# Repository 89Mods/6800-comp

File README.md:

# 6800-comp

Computer with a 6800 (or 6809) CPU. See [here](https://tholin.dev/6800/) for more information.

`Emu` contains an emulation of the computer (6800 mode only) written in C++.

`Hardware` contains the KiCad projects for all the boards.

`Kernal` contains the kernal sources that go on the EPROM.

`Software` contains all kinds of software I’ve written for this computer.

The [ASL Assembler](https://github.com/Macroassembler-AS/asl-releases) is required to build all code in this project.

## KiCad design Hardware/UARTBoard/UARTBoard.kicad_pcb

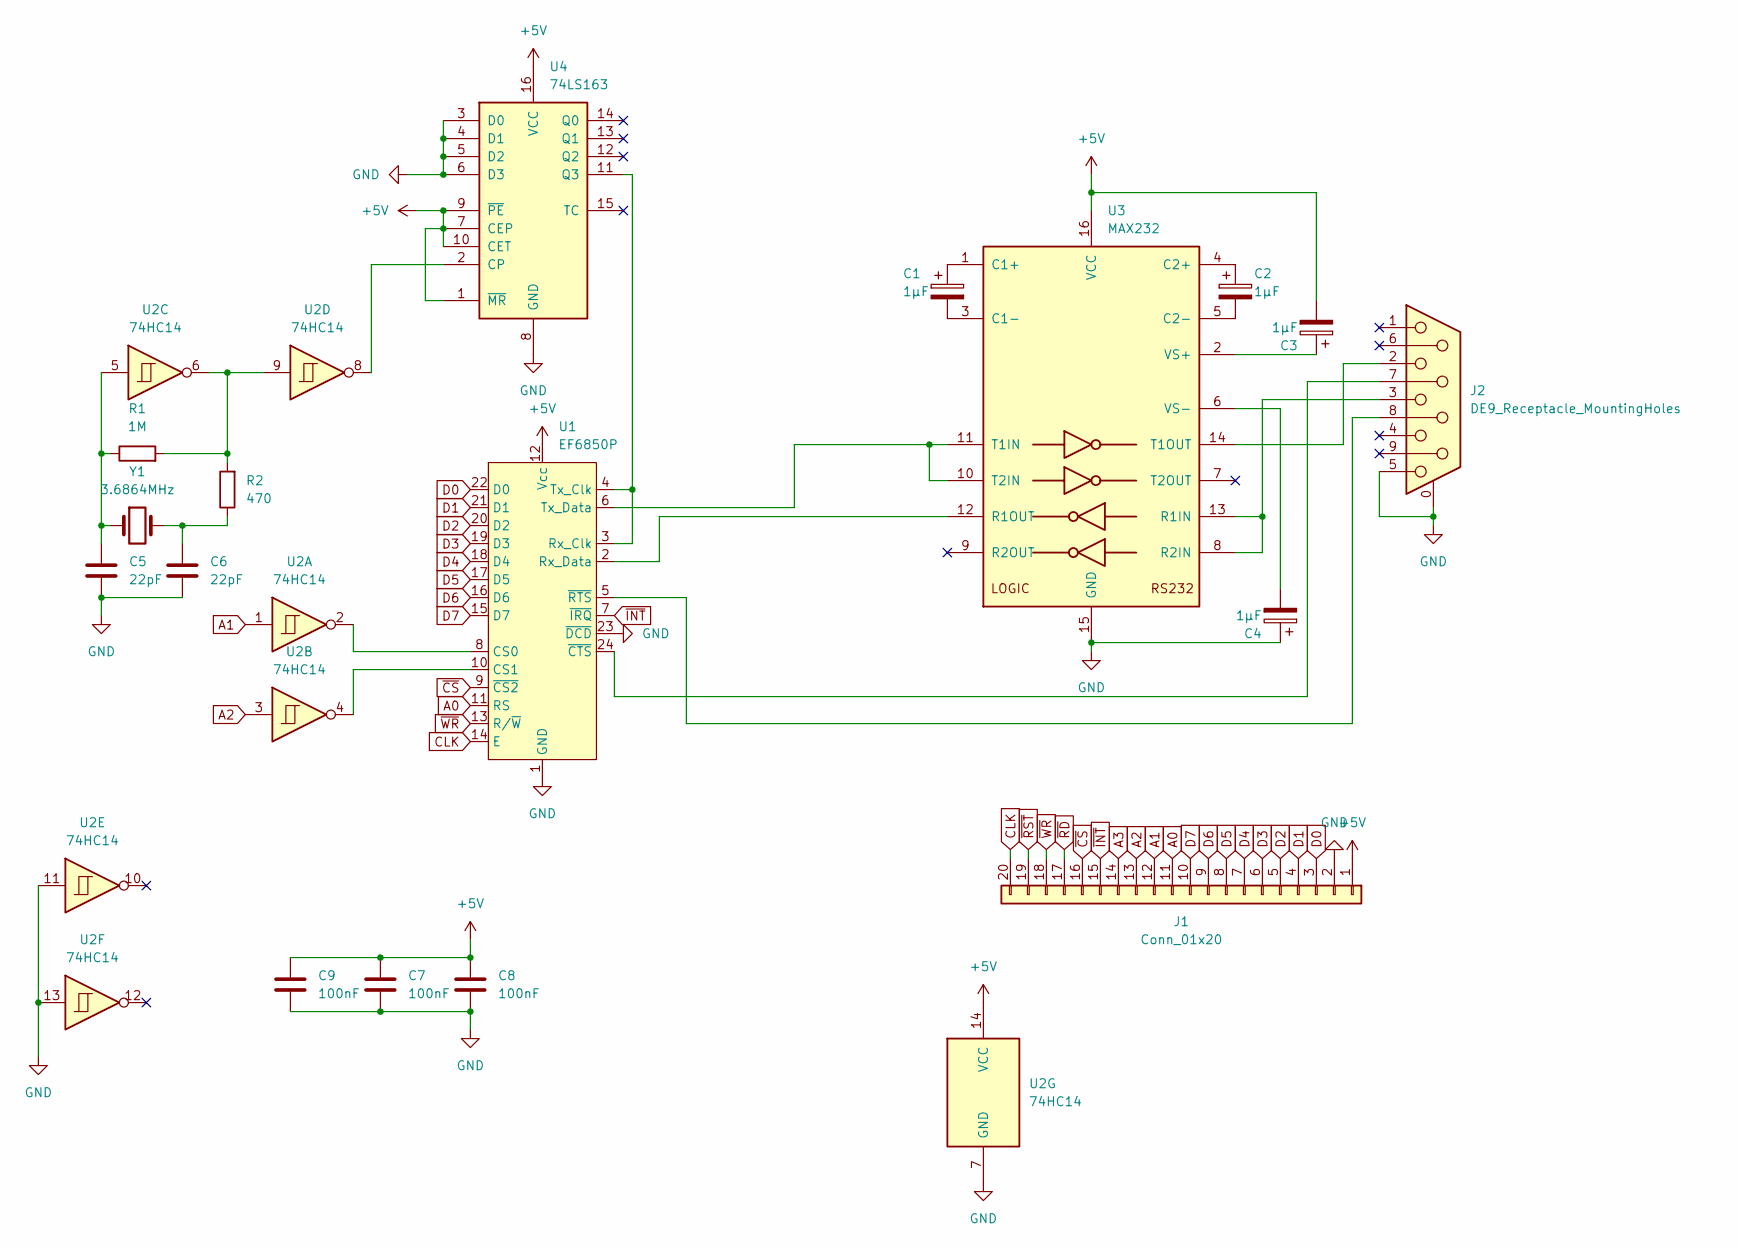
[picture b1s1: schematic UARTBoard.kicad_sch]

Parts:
C1, C2, C3, C4: 1µF; CP_Radial_D4.0mm_P2.00mm
C5, C6: 22pF; C_Disc_D3.0mm_W1.6mm_P2.50mm
C7, C8, C9: 100nF; C_Disc_D3.0mm_W1.6mm_P2.50mm
J1: Conn_01x20; PinHeader_1x20_P2.54mm_Vertical
J2: DE9_Receptacle_MountingHoles; DSUB-9_Female_Horizontal_P2.77x2.84mm_EdgePinOffset4.94mm_H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
R1: 1M; R_Axial_DIN0204_L3.6mm_D1.6mm_P7.62mm_Horizontal
R2: 470; R_Axial_DIN0204_L3.6mm_D1.6mm_P7.62mm_Horizontal
U1: EF6850P; DIP-24_W15.24mm
U2: 74HC14; DIP-14_W7.62mm
U3: MAX232; DIP-16_W7.62mm
U4: 74LS163; DIP-16_W7.62mm
Y1: 3.6864MHz; Crystal_HC18-U_Vertical

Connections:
+5V: C3.2, C7.1, C8.1, C9.1, J1.1, U1.12 (Vcc), U2.14 (VCC), U3.16 (VCC), U4.1 (~MR), U4.7 (CEP), U4.9 (~PE), U4.10 (CET), U4.16 (VCC)
A0: J1.11, U1.11 (RS)
A1: J1.12, U2.1
A2: J1.13, U2.3
A3: J1.14
CLK: J1.20, U1.14 (E)
D0: J1.3, U1.22 (D0)
D1: J1.4, U1.21 (D1)
D2: J1.5, U1.20 (D2)
D3: J1.6, U1.19 (D3)
D4: J1.7, U1.18 (D4)
D5: J1.8, U1.17 (D5)
D6: J1.9, U1.16 (D6)
D7: J1.10, U1.15 (D7)
GND: C4.1, C5.2, C6.2, C7.2, C8.2, C9.2, J1.2, J2.0 (PAD), J2.5, U1.1 (GND), U1.23 (~DCD), U2.7 (GND), U2.11, U2.13, U3.15 (GND), U4.3 (D0), U4.4 (D1), U4.5 (D2), U4.6 (D3), U4.8 (GND)
unnamed: C5.1, R1.1, U2.5, Y1.1
unnamed: C6.1, R2.1, Y1.2
unnamed: R1.2, R2.2, U2.6, U2.9
unnamed: U1.8 (CS0), U2.2
unnamed: U1.10 (CS1), U2.4
unnamed: U1.3 (Rx_Clk), U1.4 (Tx_Clk), U4.11 (Q3)
unnamed: U1.2 (Rx_Data), U3.12 (R1OUT)
unnamed: U1.6 (Tx_Data), U3.10 (T2IN), U3.11 (T1IN)
unnamed: J2.7, U1.24 (~CTS)
unnamed: J2.8, U1.5 (~RTS)
unnamed: C1.1, U3.1 (C1+)
unnamed: C1.2, U3.3 (C1-)
unnamed: C2.1, U3.4 (C2+)
unnamed: C2.2, U3.5 (C2-)
unnamed: J2.3, U3.8 (R2IN), U3.13 (R1IN)
unnamed: J2.2, U3.14 (T1OUT)
unnamed: C3.1, U3.2 (VS+)
unnamed: C4.2, U3.6 (VS-)
unnamed: U2.8, U4.2 (CP)
~CS: J1.16, U1.9 (~CS2)
~INT: J1.15, U1.7 (~IRQ)
~RD: J1.17
~RST: J1.19
~WR: J1.18, U1.13 (R/~W)

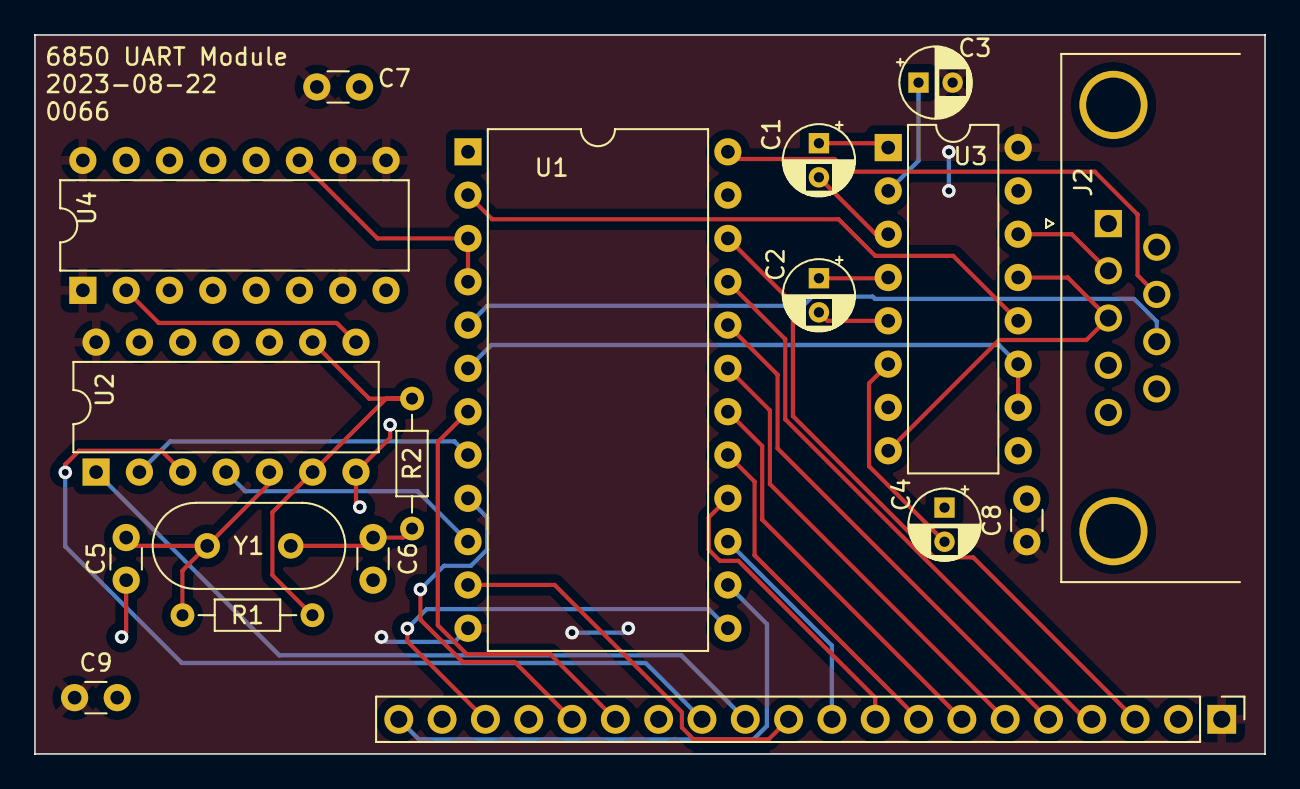
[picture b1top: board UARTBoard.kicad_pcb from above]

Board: 2 copper layers, 72.1 x 42.2 mm, 18 parts (0 on the bottom side), 36 nets.

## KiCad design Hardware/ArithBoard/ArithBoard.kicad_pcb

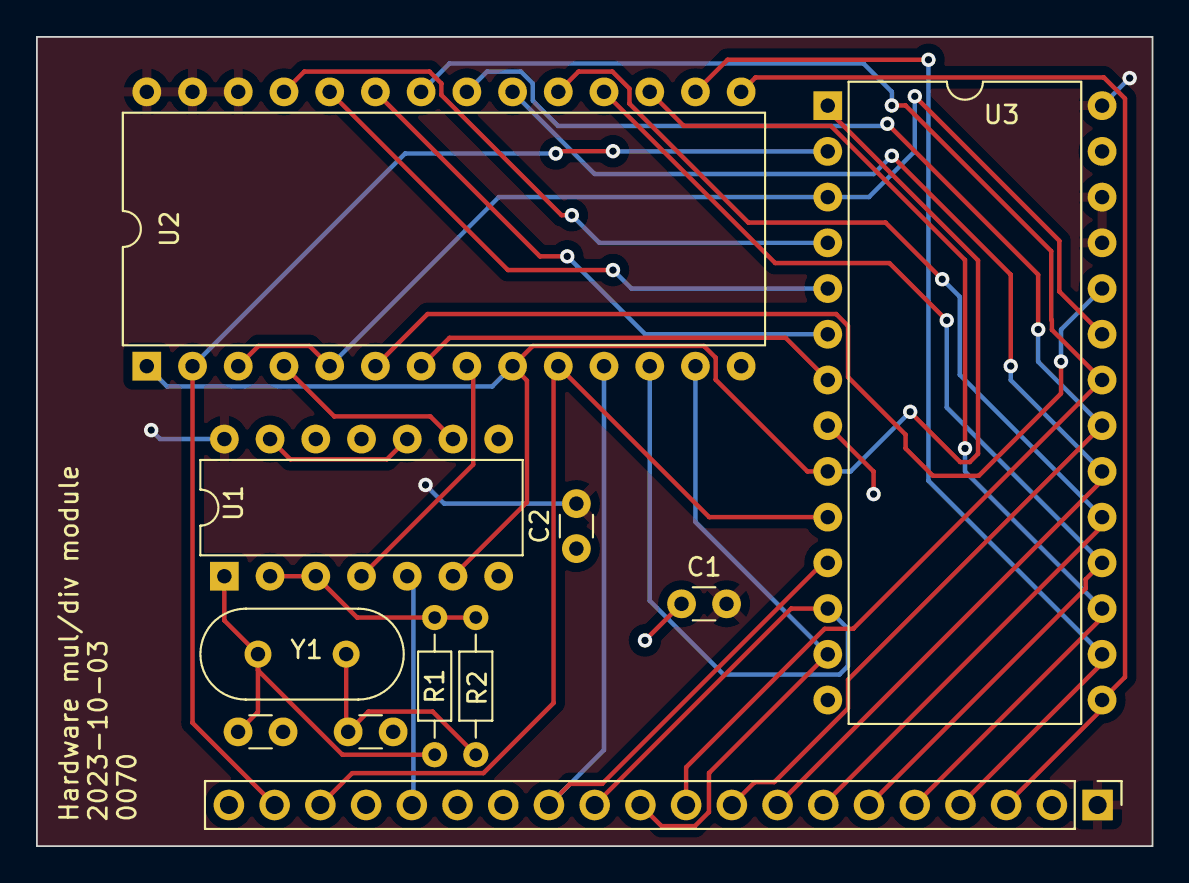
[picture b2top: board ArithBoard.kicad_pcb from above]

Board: 2 copper layers, 62.0 x 45.0 mm, 11 parts (0 on the bottom side), 29 nets.

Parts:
C1, C2: 100nF; C_Disc_D3.0mm_W1.6mm_P2.50mm
C3, C4: 22pF; C_Disc_D3.0mm_W1.6mm_P2.50mm
J1: Conn_01x20; PinHeader_1x20_P2.54mm_Vertical
R1: 1M; R_Axial_DIN0204_L3.6mm_D1.6mm_P7.62mm_Horizontal
R2: 470; R_Axial_DIN0204_L3.6mm_D1.6mm_P7.62mm_Horizontal
U1: 74HC14; DIP-14_W7.62mm
U2, U3: CDP1855; DIP-28_W15.24mm
Y1: 3.6864MHz; Crystal_HC18-U_Vertical

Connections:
+5V: C1.2, C2.2, J1.1, U1.14 (VCC), U2.26 (CN1), U2.27 (CN0), U2.28 (Vdd), U3.25 (~CI), U3.26 (CN1), U3.28 (Vdd)
A0: J1.11, U2.13 (RA0), U3.13 (RA0)
A1: J1.12, U2.12 (RA1), U3.12 (RA1)
A2: J1.13, U2.11 (RA2), U3.11 (RA2)
CS: U1.6, U2.1 (CE), U2.9 (STB), U3.1 (CE), U3.9 (STB)
D0: J1.3, U2.15 (BUS0), U3.15 (BUS0)
D1: J1.4, U2.16 (BUS1), U3.16 (BUS1)
D2: J1.5, U2.17 (BUS2), U3.17 (BUS2)
D3: J1.6, U2.18 (BUS3), U3.18 (BUS3)
D4: J1.7, U2.19 (BUS4), U3.19 (BUS4)
D5: J1.8, U2.20 (BUS5), U3.20 (BUS5)
D6: J1.9, U2.21 (BUS6), U3.21 (BUS6)
D7: J1.10, U2.22 (BUS7), U3.22 (BUS7)
GND: C1.1, C2.1, C3.2, C4.2, J1.2, U1.7 (GND), U1.11, U2.14 (GND), U3.8 (CLK), U3.14 (GND), U3.27 (CN0)
unnamed: C3.1, R1.1, U1.1, Y1.1
unnamed: C4.1, R2.1, Y1.2
unnamed: R1.2, R2.2, U1.2, U1.3
unnamed: U1.10, U1.13
unnamed: U1.4, U2.8 (CLK)
unnamed: U2.3 (CTL), U2.5 (Y_L), U3.3 (CTL), U3.23 (Z_R)
unnamed: U2.24 (Y_R), U3.5 (Y_L)
unnamed: U2.6 (Z_L), U3.24 (Y_R)
unnamed: U2.23 (Z_R), U3.6 (Z_L)
unnamed: U2.25 (~CI), U3.4 (~CO/~OF)
unnamed: U1.9, U2.4 (~CO/~OF)
unnamed: U2.7 (~SHIFT), U3.7 (~SHIFT)
~CS: J1.16, U1.5
~RESET: J1.19, U2.2 (~CLEAR), U3.2 (~CLEAR)
~WR: J1.18, U2.10 (RD/~WE), U3.10 (RD/~WE)

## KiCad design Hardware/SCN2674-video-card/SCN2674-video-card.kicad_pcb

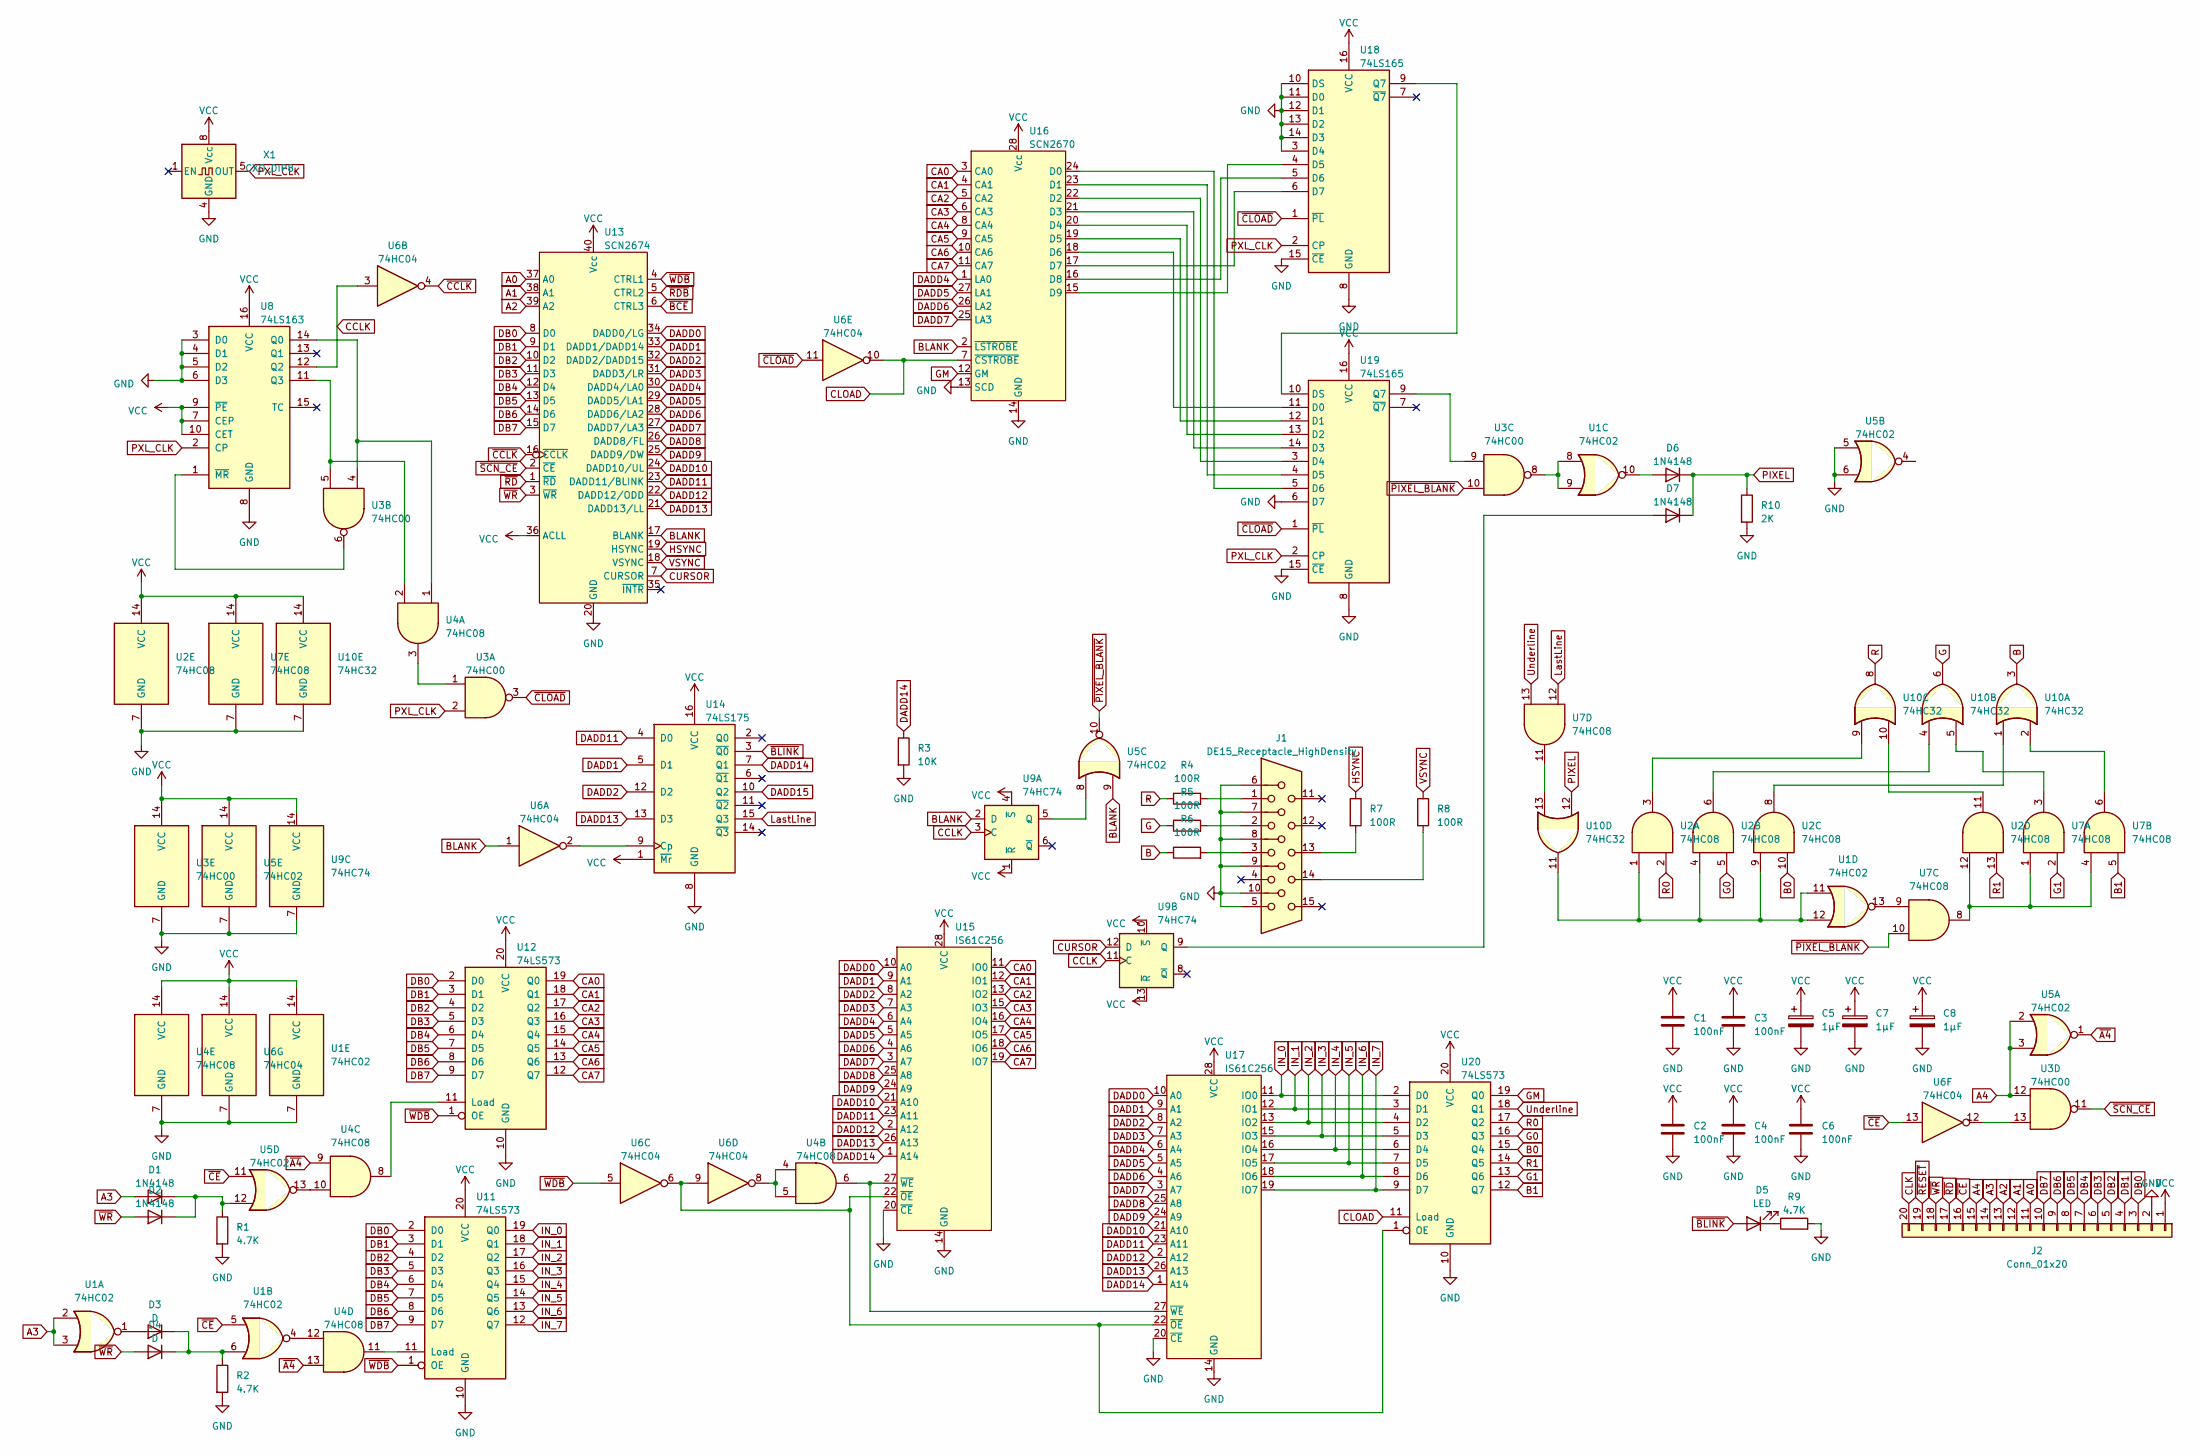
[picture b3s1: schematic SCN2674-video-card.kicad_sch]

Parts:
C1, C2, C3, C4, C6: 100nF; C_Axial_L5.1mm_D3.1mm_P7.50mm_Horizontal
C5, C7, C8: 1µF; CP_Radial_D4.0mm_P2.00mm
D1, D2, D6, D7: 1N4148; D_DO-34_SOD68_P7.62mm_Horizontal
D3, D4: D; D_DO-34_SOD68_P7.62mm_Horizontal
D5: LED; LED_D3.0mm
J1: DE15_Receptacle_HighDensity; DSUB-15-HD_Female_Horizontal_P2.29x1.98mm_EdgePinOffset3.03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
J2: Conn_01x20; PinHeader_1x20_P2.54mm_Vertical
R1, R2, R9: 4.7K; R_Axial_DIN0204_L3.6mm_D1.6mm_P7.62mm_Horizontal
R3: 10K; R_Axial_DIN0204_L3.6mm_D1.6mm_P7.62mm_Horizontal
R4, R5, R6, R7, R8: 100R; R_Axial_DIN0204_L3.6mm_D1.6mm_P7.62mm_Horizontal
R10: 2K; R_Axial_DIN0204_L3.6mm_D1.6mm_P7.62mm_Horizontal
U1, U5: 74HC02; DIP-14_W7.62mm
U2, U4, U7: 74HC08; DIP-14_W7.62mm
U3: 74HC00; DIP-14_W7.62mm
U6: 74HC04; DIP-14_W7.62mm
U8: 74LS163; DIP-16_W7.62mm
U9: 74HC74; DIP-14_W7.62mm
U10: 74HC32; DIP-14_W7.62mm
U11, U12, U20: 74LS573; DIP-20_W7.62mm
U13: SCN2674; DIP-40_W15.24mm
U14: 74LS175; DIP-16_W7.62mm
U15, U17: IS61C256; DIP-28_W7.62mm
U16: SCN2670; DIP-28_W15.24mm
U18, U19: 74LS165; DIP-16_W7.62mm
X1: CXO_DIP8; Oscillator_DIP-8

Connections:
A0: J2.11, U13.37 (A0)
A1: J2.12, U13.38 (A1)
A2: J2.13, U13.39 (A2)
A3: D1.2 (A), J2.14, U1.2, U1.3
A4: J2.15, U3.12, U5.2, U5.3
B: R6.1, U10.3
B0: U2.10, U20.15 (Q4)
B1: U7.5, U20.12 (Q7)
BLANK: U5.9, U6.1, U9.2 (D), U13.17 (BLANK), U16.2 (~LSTROBE)
CA0: U12.19 (Q0), U15.11 (IO0), U16.3 (CA0)
CA1: U12.18 (Q1), U15.12 (IO1), U16.4 (CA1)
CA2: U12.17 (Q2), U15.13 (IO2), U16.5 (CA2)
CA3: U12.16 (Q3), U15.15 (IO3), U16.6 (CA3)
CA4: U12.15 (Q4), U15.16 (IO4), U16.8 (CA4)
CA5: U12.14 (Q5), U15.17 (IO5), U16.9 (CA5)
CA6: U12.13 (Q6), U15.18 (IO6), U16.10 (CA6)
CA7: U12.12 (Q7), U15.19 (IO7), U16.11 (CA7)
CCLK: U6.3, U8.12 (Q2), U9.3 (C), U9.11 (C)
CLK: J2.20
CLOAD: U6.10, U16.7 (~CSTROBE), U20.11 (Load)
CURSOR: U9.12 (D), U13.7 (CURSOR)
DADD0: U13.34 (DADD0/LG), U15.10 (A0), U17.10 (A0)
DADD1: U13.33 (DADD1/DADD14), U14.5 (D1), U15.9 (A1), U17.9 (A1)
DADD2: U13.32 (DADD2/DADD15), U14.12 (D2), U15.8 (A2), U17.8 (A2)
DADD3: U13.31 (DADD3/LR), U15.7 (A3), U17.7 (A3)
DADD4: U13.30 (DADD4/LA0), U15.6 (A4), U16.1 (LA0), U17.6 (A4)
DADD5: U13.29 (DADD5/LA1), U15.5 (A5), U16.27 (LA1), U17.5 (A5)
DADD6: U13.28 (DADD6/LA2), U15.4 (A6), U16.26 (LA2), U17.4 (A6)
DADD7: U13.27 (DADD7/LA3), U15.3 (A7), U16.25 (LA3), U17.3 (A7)
DADD8: U13.26 (DADD8/FL), U15.25 (A8), U17.25 (A8)
DADD9: U13.25 (DADD9/DW), U15.24 (A9), U17.24 (A9)
DADD10: U13.24 (DADD10/UL), U15.21 (A10), U17.21 (A10)
DADD11: U13.23 (DADD11/BLINK), U14.4 (D0), U15.23 (A11), U17.23 (A11)
DADD12: U13.22 (DADD12/ODD), U15.2 (A12), U17.2 (A12)
DADD13: U13.21 (DADD13/LL), U14.13 (D3), U15.26 (A13), U17.26 (A13)
DADD14: R3.1, U14.7 (Q1), U15.1 (A14), U17.1 (A14)
DADD15: U14.10 (Q2)
DB0: J2.3, U11.2 (D0), U12.2 (D0), U13.8 (D0)
DB1: J2.4, U11.3 (D1), U12.3 (D1), U13.9 (D1)
DB2: J2.5, U11.4 (D2), U12.4 (D2), U13.10 (D2)
DB3: J2.6, U11.5 (D3), U12.5 (D3), U13.11 (D3)
DB4: J2.7, U11.6 (D4), U12.6 (D4), U13.12 (D4)
DB5: J2.8, U11.7 (D5), U12.7 (D5), U13.13 (D5)
DB6: J2.9, U11.8 (D6), U12.8 (D6), U13.14 (D6)
DB7: J2.10, U11.9 (D7), U12.9 (D7), U13.15 (D7)
G: R5.1, U10.6
G0: U2.5, U20.16 (Q3)
G1: U7.2, U20.13 (Q6)
GM: U16.12 (GM), U20.19 (Q0)
GND: C1.2, C2.2, C3.2, C4.2, C5.2, C6.2, C7.2, C8.2, J1.5, J1.6, J1.7, J1.8, J1.9, J1.10, J2.2, R1.2, R2.2, R3.2, R9.2, R10.2, U1.7 (GND), U2.7 (GND), U3.7 (GND), U4.7 (GND), U5.5, U5.6, U5.7 (GND), U6.7 (GND), U7.7 (GND), U8.3 (D0), U8.4 (D1), U8.5 (D2), U8.6 (D3), U8.8 (GND), U9.7 (GND), U10.7 (GND), U11.10 (GND), U12.10 (GND), U13.20 (GND), U14.8 (GND), U15.14 (GND), U15.20 (~CE), U16.13 (SCD), U16.14 (GND), U17.14 (GND), U17.20 (~CE), U18.3 (D4), U18.8 (GND), U18.10 (DS), U18.11 (D0), U18.12 (D1), U18.13 (D2), U18.14 (D3), U18.15 (~CE), U19.6 (D7), U19.8 (GND), U19.15 (~CE), U20.10 (GND), X1.4 (GND)
HSYNC: R7.1, U13.19 (HSYNC)
IN_0: U11.19 (Q0), U17.11 (IO0), U20.2 (D0)
IN_1: U11.18 (Q1), U17.12 (IO1), U20.3 (D1)
IN_2: U11.17 (Q2), U17.13 (IO2), U20.4 (D2)
IN_3: U11.16 (Q3), U17.15 (IO3), U20.5 (D3)
IN_4: U11.15 (Q4), U17.16 (IO4), U20.6 (D4)
IN_5: U11.14 (Q5), U17.17 (IO5), U20.7 (D5)
IN_6: U11.13 (Q6), U17.18 (IO6), U20.8 (D6)
IN_7: U11.12 (Q7), U17.19 (IO7), U20.9 (D7)
LastLine: U7.12, U14.15 (Q3)
unnamed: D1.1 (K), D2.1 (K), R1.1, U5.12
unnamed: D3.2 (A), U1.1
unnamed: D3.1 (K), D4.1 (K), R2.1, U1.6
unnamed: D5.1 (K), R9.1
unnamed: D6.2 (A), U1.10
unnamed: D7.2 (A), U9.9 (Q)
unnamed: J1.1, R4.2
unnamed: J1.2, R5.2
unnamed: J1.3, R6.2
unnamed: J1.13, R7.2
unnamed: J1.14, R8.2
unnamed: U1.4, U4.12
unnamed: U1.8, U1.9, U3.8
unnamed: U1.11, U1.12, U2.1, U2.4, U2.9, U10.11
unnamed: U1.13, U7.9
unnamed: U2.12, U7.1, U7.4, U7.8
unnamed: U3.1, U4.3
unnamed: U3.13, U6.12
unnamed: U4.4, U4.5, U6.8
unnamed: U4.10, U5.13
unnamed: U3.4, U4.1, U8.14 (Q0)
unnamed: U3.5, U4.2, U8.11 (Q3)
unnamed: U3.6, U8.1 (~MR)
unnamed: U5.8, U9.5 (Q)
unnamed: U2.8, U10.1
unnamed: U7.6, U10.2
unnamed: U2.6, U10.4
unnamed: U7.3, U10.5
unnamed: U2.3, U10.9
unnamed: U2.11, U10.10
unnamed: U7.11, U10.13
unnamed: U4.11, U11.11 (Load)
unnamed: U4.8, U12.11 (Load)
unnamed: U6.2, U14.9 (Cp)
unnamed: U6.6, U6.9, U15.22 (~OE), U17.22 (~OE), U20.1 (OE)
unnamed: U4.6, U15.27 (~WE), U17.27 (~WE)
unnamed: U16.24 (D0), U19.5 (D6)
unnamed: U16.23 (D1), U19.4 (D5)
unnamed: U16.22 (D2), U19.3 (D4)
unnamed: U16.21 (D3), U19.14 (D3)
unnamed: U16.20 (D4), U19.13 (D2)
unnamed: U16.19 (D5), U19.12 (D1)
unnamed: U16.18 (D6), U19.11 (D0)
unnamed: U16.17 (D7), U18.6 (D7)
unnamed: U16.16 (D8), U18.5 (D6)
unnamed: U16.15 (D9), U18.4 (D5)
unnamed: U18.9 (Q7), U19.10 (DS)
unnamed: U3.9, U19.9 (Q7)
PIXEL: D6.1 (K), D7.1 (K), R10.1, U10.12
PXL_CLK: U3.2, U8.2 (CP), U18.2 (CP), U19.2 (CP), X1.5 (OUT)
R: R4.1, U10.8
R0: U2.2, U20.17 (Q2)
R1: U2.13, U20.14 (Q5)
Underline: U7.13, U20.18 (Q1)
VCC: C1.1, C2.1, C3.1, C4.1, C5.1, C6.1, C7.1, C8.1, J2.1, U1.14 (VCC), U2.14 (VCC), U3.14 (VCC), U4.14 (VCC), U5.14 (VCC), U6.14 (VCC), U7.14 (VCC), U8.7 (CEP), U8.9 (~PE), U8.10 (CET), U8.16 (VCC), U9.1 (~R), U9.4 (~S), U9.10 (~S), U9.13 (~R), U9.14 (VCC), U10.14 (VCC), U11.20 (VCC), U12.20 (VCC), U13.36 (ACLL), U13.40 (Vcc), U14.1 (~Mr), U14.16 (VCC), U15.28 (VCC), U16.28 (Vcc), U17.28 (VCC), U18.16 (VCC), U19.16 (VCC), U20.20 (VCC), X1.8 (Vcc)
VSYNC: R8.1, U13.18 (VSYNC)
~A4: U4.9, U4.13, U5.1
~BCE: U13.6 (CTRL3)
~BLINK: D5.2 (A), U14.3 (~Q0)
~CCLK: U6.4, U13.16 (~CCLK)
~CE: J2.16, U1.5, U5.11, U6.13
~CLOAD: U3.3, U6.11, U18.1 (~PL), U19.1 (~PL)
~PIXEL_BLANK: U3.10, U5.10, U7.10
~RDB: U13.5 (CTRL2)
~RD: J2.17, U13.1 (~RD)
~RESET: J2.19
~SCN_CE: U3.11, U13.2 (~CE)
~WDB: U6.5, U11.1 (OE), U12.1 (OE), U13.4 (CTRL1)
~WR: D2.2 (A), D4.2 (A), J2.18, U13.3 (~WR)

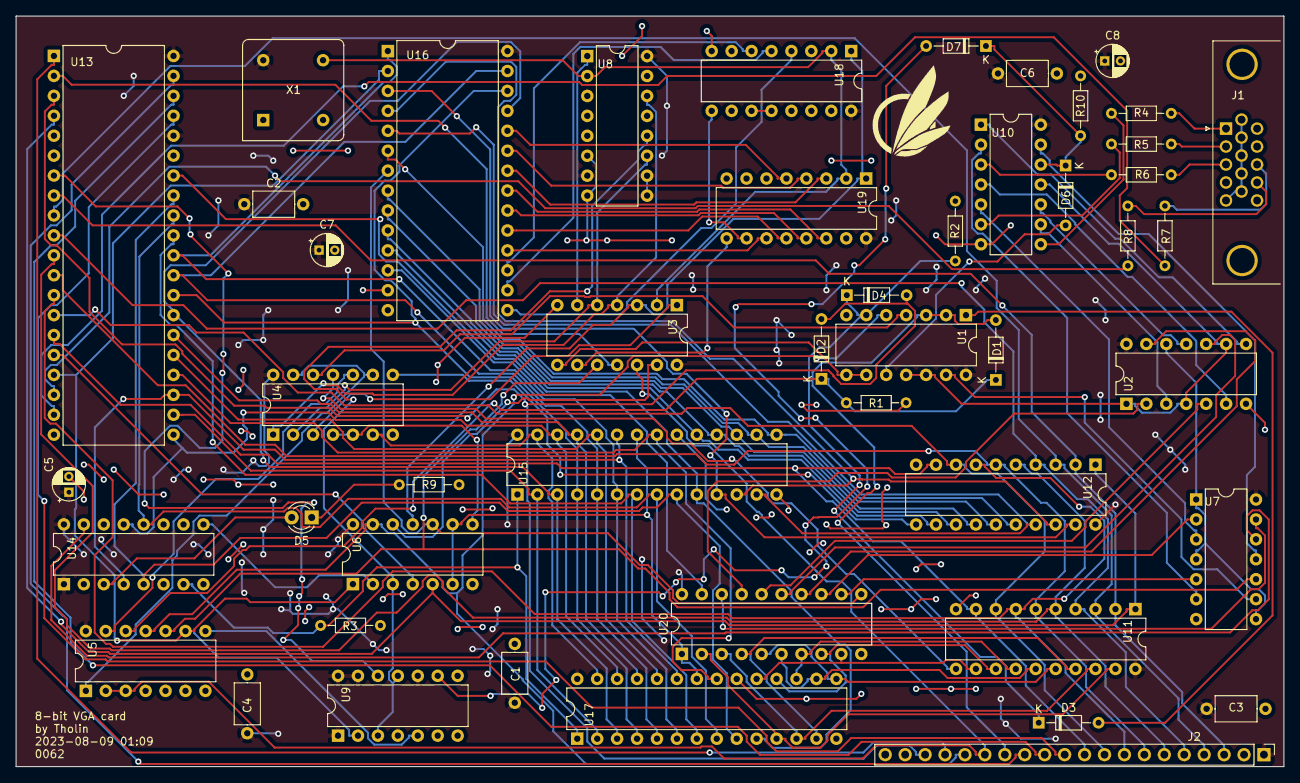
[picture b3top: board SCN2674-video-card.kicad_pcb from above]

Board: 2 copper layers, 161.5 x 95.6 mm, 48 parts (0 on the bottom side), 124 nets.

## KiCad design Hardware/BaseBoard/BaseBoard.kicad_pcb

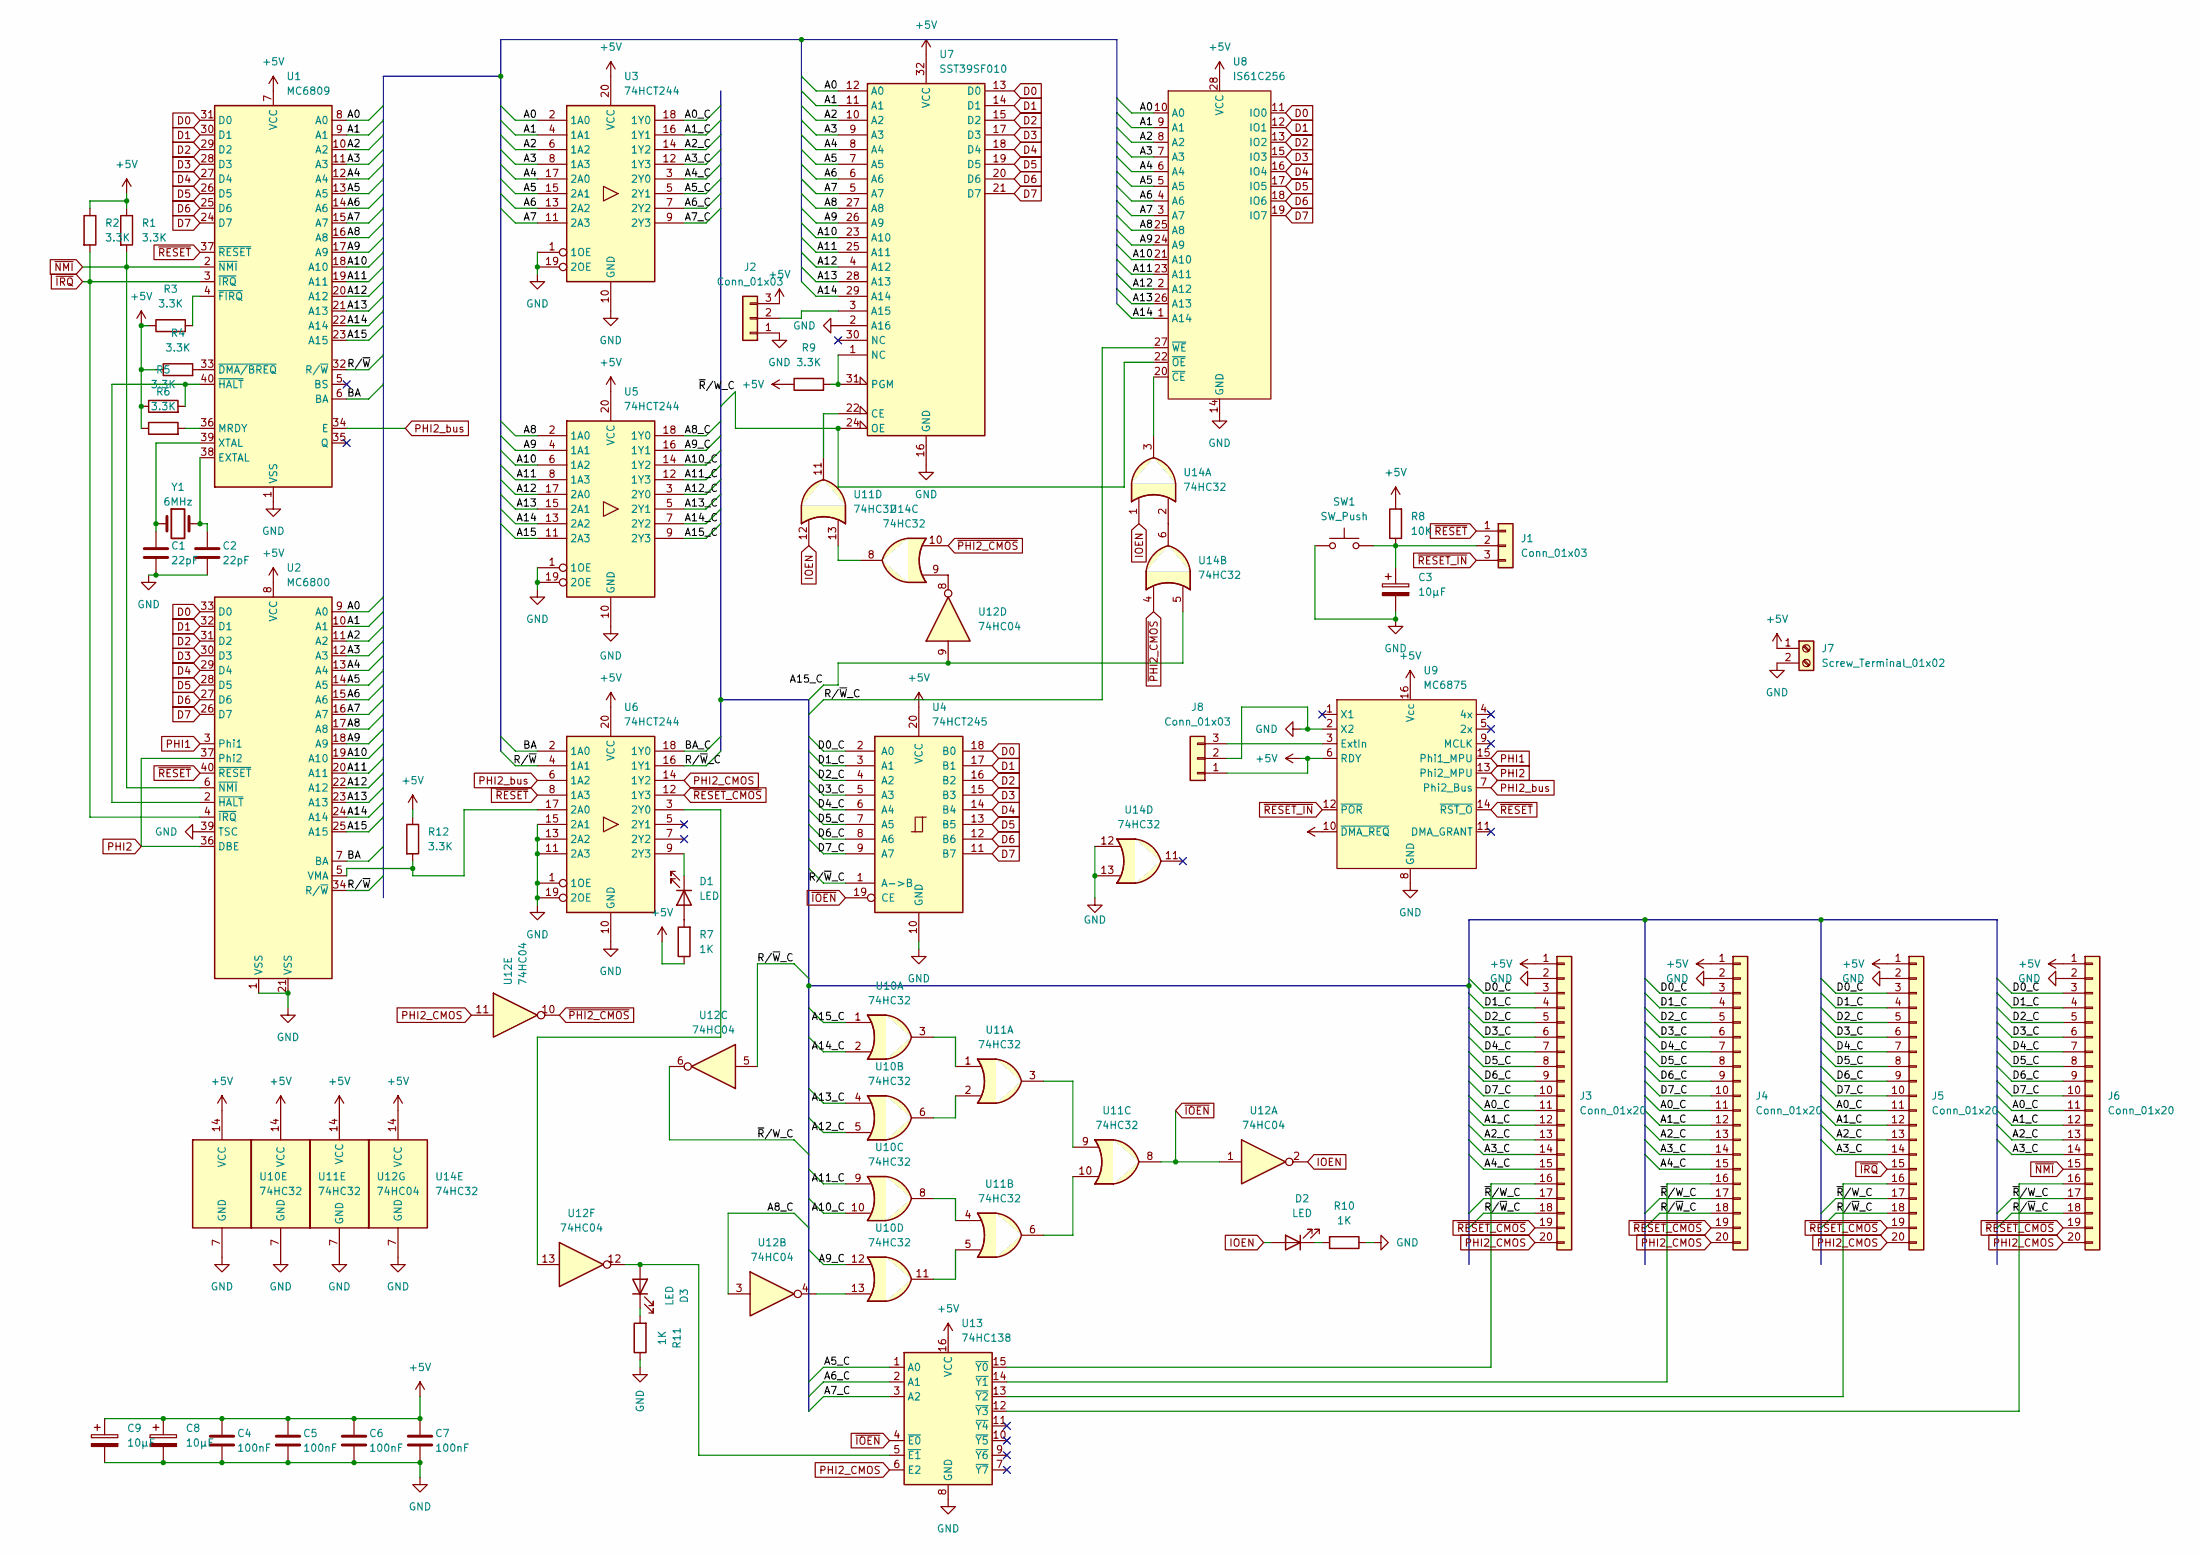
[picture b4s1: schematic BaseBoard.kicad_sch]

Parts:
C1, C2: 22pF; C_Disc_D3.0mm_W1.6mm_P2.50mm
C3, C8, C9: 10µF; CP_Radial_D4.0mm_P2.00mm
C4, C5, C6, C7: 100nF; C_Disc_D3.0mm_W1.6mm_P2.50mm
D1: LED; LED_D3.0mm
D2, D3: LED; LED_1206_3216Metric_Pad1.42x1.75mm_HandSolder
J1, J2, J8: Conn_01x03; PinHeader_1x03_P2.54mm_Vertical
J3, J4, J5, J6: Conn_01x20; PinSocket_1x20_P2.54mm_Vertical
J7: Screw_Terminal_01x02; TerminalBlock_bornier-2_P5.08mm
R1, R2, R3, R4, R5, R6, R9, R12: 3.3K; R_Axial_DIN0204_L3.6mm_D1.6mm_P7.62mm_Horizontal
R7: 1K; R_Axial_DIN0204_L3.6mm_D1.6mm_P7.62mm_Horizontal
R8: 10K; R_Axial_DIN0204_L3.6mm_D1.6mm_P7.62mm_Horizontal
R10, R11: 1K; R_1206_3216Metric_Pad1.30x1.75mm_HandSolder
SW1: SW_Push; SW_PUSH_6mm
U1: MC6809; DIP-40_W15.24mm
U2: MC6800; DIP-40_W15.24mm
U3, U5, U6: 74HCT244; DIP-20_W7.62mm
U4: 74HCT245; DIP-20_W7.62mm
U7: SST39SF010; DIP-32_W15.24mm
U8: IS61C256; DIP-28_W7.62mm
U9: MC6875; DIP-16_W7.62mm
U10, U11, U14: 74HC32; DIP-14_W7.62mm
U12: 74HC04; DIP-14_W7.62mm
U13: 74HC138; DIP-16_W7.62mm
Y1: 6MHz; Crystal_HC18-U_Vertical

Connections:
+5V: C4.1, C5.1, C6.1, C7.1, C8.1, C9.1, J2.3, J3.1, J4.1, J5.1, J6.1, J7.1, J8.1, R1.1, R2.1, R3.1, R4.1, R5.1, R6.1, R7.1, R8.2, R9.1, R12.1, U1.7 (VCC), U2.8 (VCC), U3.20 (VCC), U4.20 (VCC), U5.20 (VCC), U6.20 (VCC), U7.32 (VCC), U8.28 (VCC), U9.6 (RDY), U9.10 (~DMA_REQ), U9.16 (Vcc), U10.14 (VCC), U11.14 (VCC), U12.14 (VCC), U13.16 (VCC), U14.14 (VCC)
/A0: U1.8 (A0), U2.9 (A0), U3.2 (1A0), U7.12 (A0), U8.10 (A0)
/A0_C: J3.11, J4.11, J5.11, J6.11, U3.18 (1Y0)
/A1: U1.9 (A1), U2.10 (A1), U3.4 (1A1), U7.11 (A1), U8.9 (A1)
/A1_C: J3.12, J4.12, J5.12, J6.12, U3.16 (1Y1)
/A2: U1.10 (A2), U2.11 (A2), U3.6 (1A2), U7.10 (A2), U8.8 (A2)
/A2_C: J3.13, J4.13, J5.13, J6.13, U3.14 (1Y2)
/A3: U1.11 (A3), U2.12 (A3), U3.8 (1A3), U7.9 (A3), U8.7 (A3)
/A3_C: J3.14, J4.14, J5.14, J6.14, U3.12 (1Y3)
/A4: U1.12 (A4), U2.13 (A4), U3.17 (2A0), U7.8 (A4), U8.6 (A4)
/A4_C: J3.15, J4.15, U3.3 (2Y0)
/A5: U1.13 (A5), U2.14 (A5), U3.15 (2A1), U7.7 (A5), U8.5 (A5)
/A5_C: U3.5 (2Y1), U13.1 (A0)
/A6: U1.14 (A6), U2.15 (A6), U3.13 (2A2), U7.6 (A6), U8.4 (A6)
/A6_C: U3.7 (2Y2), U13.2 (A1)
/A7: U1.15 (A7), U2.16 (A7), U3.11 (2A3), U7.5 (A7), U8.3 (A7)
/A7_C: U3.9 (2Y3), U13.3 (A2)
/A8: U1.16 (A8), U2.17 (A8), U5.2 (1A0), U7.27 (A8), U8.25 (A8)
/A8_C: U5.18 (1Y0), U12.3
/A9: U1.17 (A9), U2.18 (A9), U5.4 (1A1), U7.26 (A9), U8.24 (A9)
/A9_C: U5.16 (1Y1), U10.12
/A10: U1.18 (A10), U2.19 (A10), U5.6 (1A2), U7.23 (A10), U8.21 (A10)
/A10_C: U5.14 (1Y2), U10.10
/A11: U1.19 (A11), U2.20 (A11), U5.8 (1A3), U7.25 (A11), U8.23 (A11)
/A11_C: U5.12 (1Y3), U10.9
/A12: U1.20 (A12), U2.22 (A12), U5.17 (2A0), U7.4 (A12), U8.2 (A12)
/A12_C: U5.3 (2Y0), U10.5
/A13: U1.21 (A13), U2.23 (A13), U5.15 (2A1), U7.28 (A13), U8.26 (A13)
/A13_C: U5.5 (2Y1), U10.4
/A14: U1.22 (A14), U2.24 (A14), U5.13 (2A2), U7.29 (A14), U8.1 (A14)
/A14_C: U5.7 (2Y2), U10.2
/A15: U1.23 (A15), U2.25 (A15), U5.11 (2A3)
/A15_C: U5.9 (2Y3), U10.1, U12.9, U14.5
/BA: U1.6 (BA), U2.7 (BA), U6.2 (1A0)
/BA_C: U6.18 (1Y0)
/D0_C: J3.3, J4.3, J5.3, J6.3, U4.2 (A0)
/D1_C: J3.4, J4.4, J5.4, J6.4, U4.3 (A1)
/D2_C: J3.5, J4.5, J5.5, J6.5, U4.4 (A2)
/D3_C: J3.6, J4.6, J5.6, J6.6, U4.5 (A3)
/D4_C: J3.7, J4.7, J5.7, J6.7, U4.6 (A4)
/D5_C: J3.8, J4.8, J5.8, J6.8, U4.7 (A5)
/D6_C: J3.9, J4.9, J5.9, J6.9, U4.8 (A6)
/D7_C: J3.10, J4.10, J5.10, J6.10, U4.9 (A7)
/R/~W: U1.32 (R/~W), U2.34 (R/~W), U6.4 (1A1)
/R/~W_C: J3.18, J4.18, J5.18, J6.18, U4.1 (A->B), U6.16 (1Y1), U8.27 (~WE), U12.5
/~R/W_C: J3.17, J4.17, J5.17, J6.17, U7.24 (OE), U8.22 (~OE), U12.6
D0: U1.31 (D0), U2.33 (D0), U4.18 (B0), U7.13 (D0), U8.11 (IO0)
D1: U1.30 (D1), U2.32 (D1), U4.17 (B1), U7.14 (D1), U8.12 (IO1)
D2: U1.29 (D2), U2.31 (D2), U4.16 (B2), U7.15 (D2), U8.13 (IO2)
D3: U1.28 (D3), U2.30 (D3), U4.15 (B3), U7.17 (D3), U8.15 (IO3)
D4: U1.27 (D4), U2.29 (D4), U4.14 (B4), U7.18 (D4), U8.16 (IO4)
D5: U1.26 (D5), U2.28 (D5), U4.13 (B5), U7.19 (D5), U8.17 (IO5)
D6: U1.25 (D6), U2.27 (D6), U4.12 (B6), U7.20 (D6), U8.18 (IO6)
D7: U1.24 (D7), U2.26 (D7), U4.11 (B7), U7.21 (D7), U8.19 (IO7)
IOEN: D2.2 (A), U11.12, U12.2, U14.1
unnamed: D1.2 (A), R7.2
unnamed: D1.1 (K), U6.9 (2Y3)
unnamed: D2.1 (K), R10.2
unnamed: D3.1 (K), R11.2
unnamed: C3.1, J1.2, R8.1, SW1.2
unnamed: J2.2, U7.3 (A15)
unnamed: J3.16, U13.15 (~Y0)
unnamed: J4.16, U13.14 (~Y1)
unnamed: J5.16, U13.13 (~Y2)
unnamed: J6.16, U13.12 (~Y3)
unnamed: J8.3, U9.3 (ExtIn)
unnamed: C2.1, U1.38 (EXTAL), Y1.2
unnamed: R6.2, U1.36 (MRDY)
unnamed: C1.1, U1.39 (XTAL), Y1.1
unnamed: R4.2, U1.33 (~DMA/BREQ)
unnamed: R3.2, U1.4 (~FIRQ)
unnamed: R5.2, U1.40 (~HALT), U2.2 (~HALT)
unnamed: U7.22 (CE), U11.11
unnamed: R9.2, U7.1 (NC), U7.31 (PGM)
unnamed: U8.20 (~CE), U14.3
unnamed: U10.3, U11.1
unnamed: U10.6, U11.2
unnamed: U10.8, U11.4
unnamed: U10.11, U11.5
unnamed: U10.13, U12.4
unnamed: U11.3, U11.9
unnamed: U11.6, U11.10
unnamed: U11.13, U14.8
unnamed: U12.8, U14.9
unnamed: U14.2, U14.6
PHI1: U2.3 (Phi1), U9.15 (Phi1_MPU)
PHI2: U2.36 (DBE), U2.37 (Phi2), U9.13 (Phi2_MPU)
PHI2_CMOS: J3.20, J4.20, J5.20, J6.20, U6.14 (1Y2), U12.11, U13.6 (E2)
PHI2_bus: U1.34 (E), U6.6 (1A2), U9.7 (Phi2_Bus)
~IOEN: U4.19 (CE), U11.8, U12.1, U13.4 (~E0)
~IRQ: J5.15, R2.2, U1.3 (~IRQ), U2.4 (~IRQ)
~NMI: J6.15, R1.2, U1.2 (~NMI), U2.6 (~NMI)
~PHI2_CMOS: U12.10, U14.4, U14.10
~RESET_CMOS: J3.19, J4.19, J5.19, J6.19, U6.12 (1Y3)
~RESET_IN: J1.3, U9.12 (~POR)
~RESET: J1.1, U1.37 (~RESET), U2.40 (~RESET), U6.8 (1A3), U9.14 (~RST_O)

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
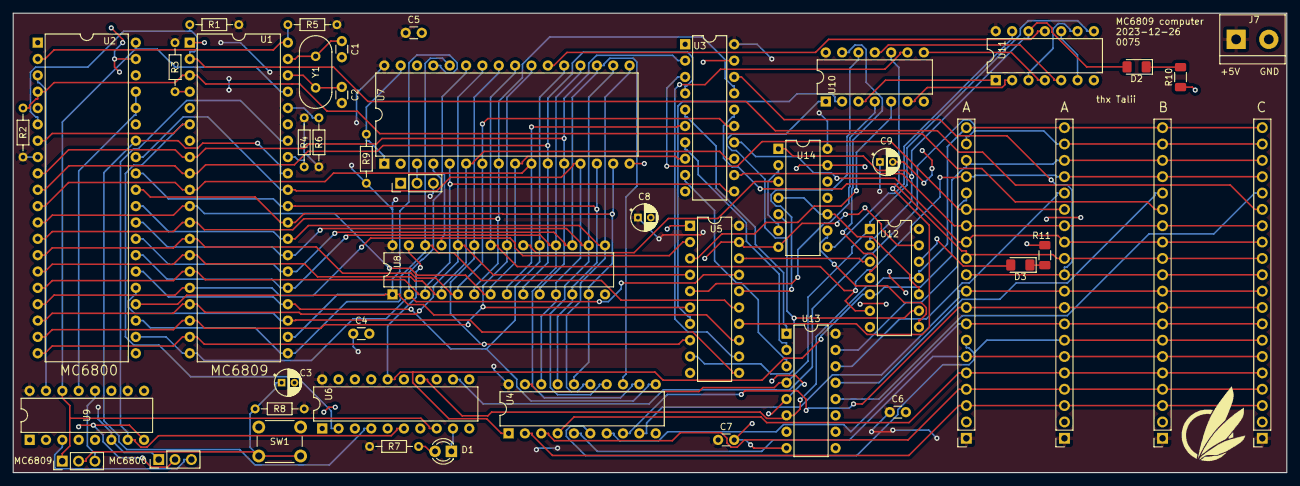
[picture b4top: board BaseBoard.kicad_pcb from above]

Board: 2 copper layers, 197.9 x 71.4 mm, 47 parts (0 on the bottom side), 97 nets.
